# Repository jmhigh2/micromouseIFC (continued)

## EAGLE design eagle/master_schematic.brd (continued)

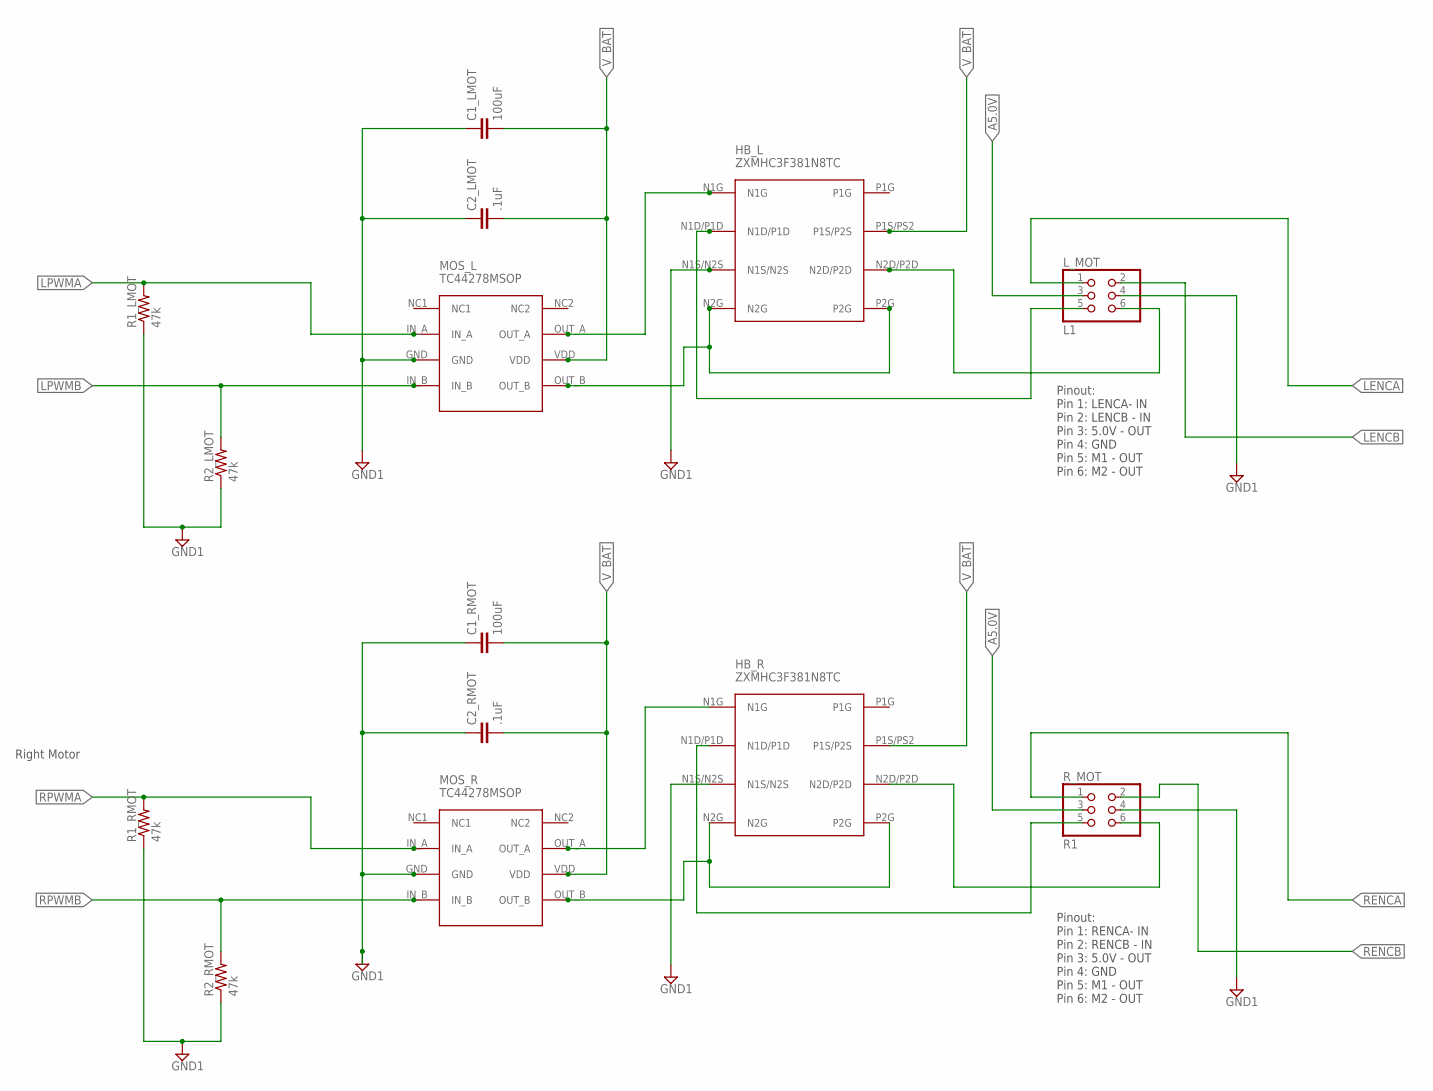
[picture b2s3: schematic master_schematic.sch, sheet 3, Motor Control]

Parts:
C1_LMOT, C1_RMOT: 100uF; C0603
C2_LMOT, C2_RMOT: .1uF; C0603
HB_L: ZXMHC3F381N8TC; 8-SOIC
HB_R: ZXMHC3F381N8TC; 8-SOIC
L_MOT: L1; 2X03
MOS_L: TC44278MSOP
MOS_R: TC44278MSOP
R1_LMOT, R1_RMOT, R2_LMOT, R2_RMOT: 47k; R0603
R_MOT: R1; 2X03

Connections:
A5.0V: L_MOT.3, R_MOT.3; also elsewhere on the board
GND1: C1_LMOT.1, C1_RMOT.1, C2_LMOT.1, C2_RMOT.1, HB_L.N1S/N2S, HB_R.N1S/N2S, L_MOT.4, MOS_L.GND, MOS_R.GND, R1_LMOT.1, R1_RMOT.1, R2_LMOT.1, R2_RMOT.1, R_MOT.4
LPWMA: MOS_L.IN_A, R1_LMOT.2; also elsewhere on the board
LPWMB: MOS_L.IN_B, R2_LMOT.2; also elsewhere on the board
L_ENC_A: L_MOT.1; also elsewhere on the board
L_ENC_B: L_MOT.2; also elsewhere on the board
unnamed: HB_L.N1G, MOS_L.OUT_A
unnamed: HB_L.N2G, HB_L.P2G, MOS_L.OUT_B
unnamed: HB_L.N1D/P1D, L_MOT.5
unnamed: HB_L.N2D/P2D, L_MOT.6
unnamed: HB_R.N1G, MOS_R.OUT_A
unnamed: HB_R.N2G, HB_R.P2G, MOS_R.OUT_B
unnamed: HB_R.N1D/P1D, R_MOT.5
unnamed: HB_R.N2D/P2D, R_MOT.6
RPWMA: MOS_R.IN_A, R1_RMOT.2; also elsewhere on the board
RPWMB: MOS_R.IN_B, R2_RMOT.2; also elsewhere on the board
R_ENC_A: R_MOT.1; also elsewhere on the board
R_ENC_B: R_MOT.2; also elsewhere on the board
V_BAT: C1_LMOT.2, C1_RMOT.2, C2_LMOT.2, C2_RMOT.2, HB_L.P1S/PS2 (P1S/P2S), HB_R.P1S/PS2 (P1S/P2S), MOS_L.VDD, MOS_R.VDD; also elsewhere on the board

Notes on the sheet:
Pinout: Pin 1: LENCA- IN Pin 2: LENCB - IN Pin 3: 5.0V - OUT Pin 4: GND Pin 5: M1 - OUT Pin 6: M2 - OUT
Right Motor
Pinout: Pin 1: RENCA- IN Pin 2: RENCB - IN Pin 3: 5.0V - OUT Pin 4: GND Pin 5: M1 - OUT Pin 6: M2 - OUT

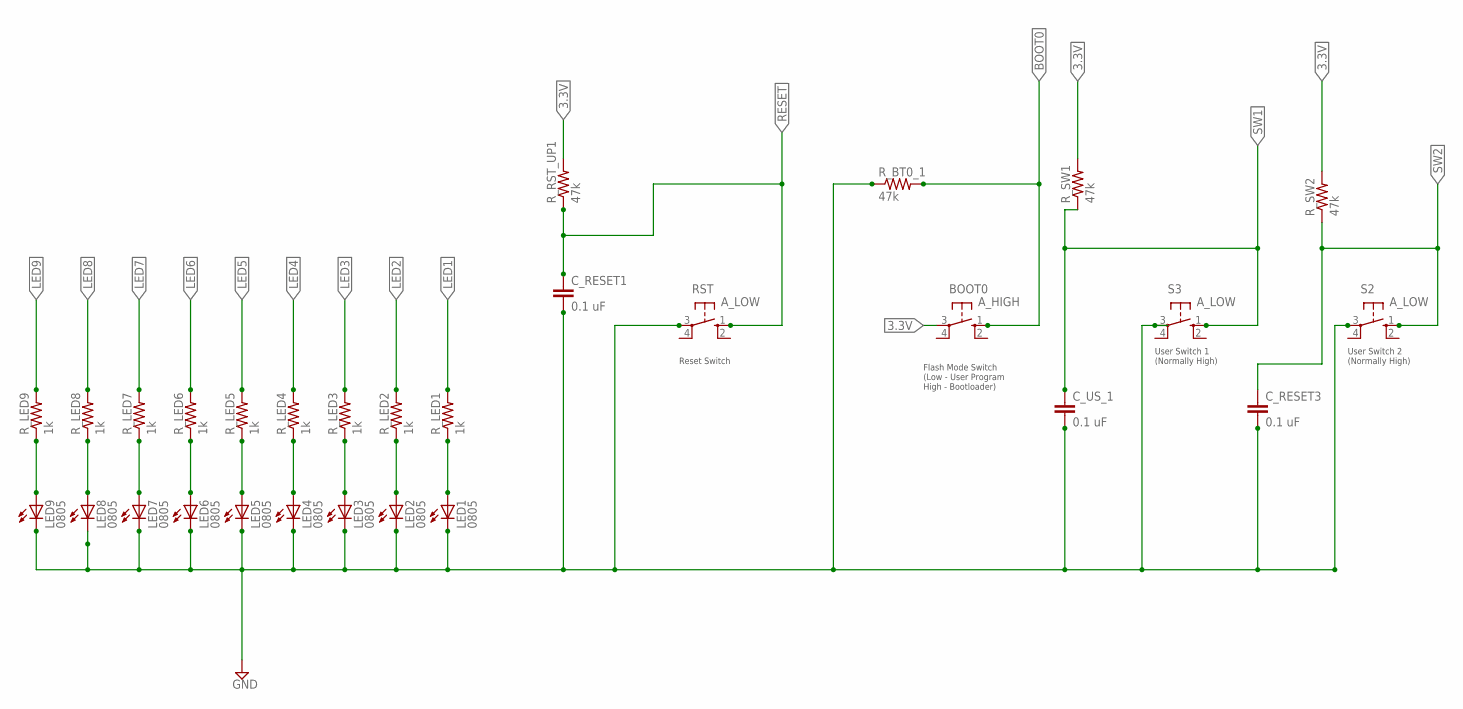
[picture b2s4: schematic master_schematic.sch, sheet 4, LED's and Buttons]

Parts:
BOOT0: A_HIGH; B3F-10XX
C_RESET1, C_RESET3: 0.1 uF; C0603
C_US_1: 0.1 uF; C0603
LED1, LED2, LED3, LED4, LED5, LED6, LED7, LED8, LED9: 0805; CHIPLED_0603
RST: A_LOW; B3F-10XX
R_BT0_1: 47k; R0603
R_LED1, R_LED2, R_LED3, R_LED4, R_LED5, R_LED6, R_LED7, R_LED8, R_LED9: 1k; R0603
R_RST_UP1: 47k; R0603
R_SW1, R_SW2: 47k; R0603
S2, S3: A_LOW; B3F-10XX

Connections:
3.3V: BOOT0.3, R_RST_UP1.2, R_SW1.2, R_SW2.2; also elsewhere on the board
BOOT0: BOOT0.1 (S), R_BT0_1.2; also elsewhere on the board
C_US_2: C_RESET3.1, R_SW2.1, S2.1 (S)
GND: C_RESET1.2, C_RESET3.2, C_US_1.2, LED1.C, LED2.C, LED3.C, LED4.C, LED5.C, LED6.C, LED7.C, LED8.C, LED9.C, RST.3, R_BT0_1.1, S2.3, S3.3; also elsewhere on the board
LED1: R_LED1.2; also elsewhere on the board
LED2: R_LED2.2; also elsewhere on the board
LED3: R_LED3.2; also elsewhere on the board
LED4: R_LED4.2; also elsewhere on the board
LED5: R_LED5.2; also elsewhere on the board
LED6: R_LED6.2; also elsewhere on the board
LED7: R_LED7.2; also elsewhere on the board
LED8: R_LED8.2; also elsewhere on the board
LED9: R_LED9.2; also elsewhere on the board
unnamed: LED1.A, R_LED1.1
unnamed: LED2.A, R_LED2.1
unnamed: LED3.A, R_LED3.1
unnamed: LED4.A, R_LED4.1
unnamed: LED5.A, R_LED5.1
unnamed: LED6.A, R_LED6.1
unnamed: LED7.A, R_LED7.1
unnamed: LED8.A, R_LED8.1
unnamed: LED9.A, R_LED9.1
RESET: C_RESET1.1, RST.1 (S), R_RST_UP1.1; also elsewhere on the board
US_1: C_US_1.1, R_SW1.1, S3.1 (S)

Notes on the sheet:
Reset Switch
Flash Mode Switch (Low - User Program High - Bootloader)
User Switch 1 (Normally High)
User Switch 2 (Normally High)

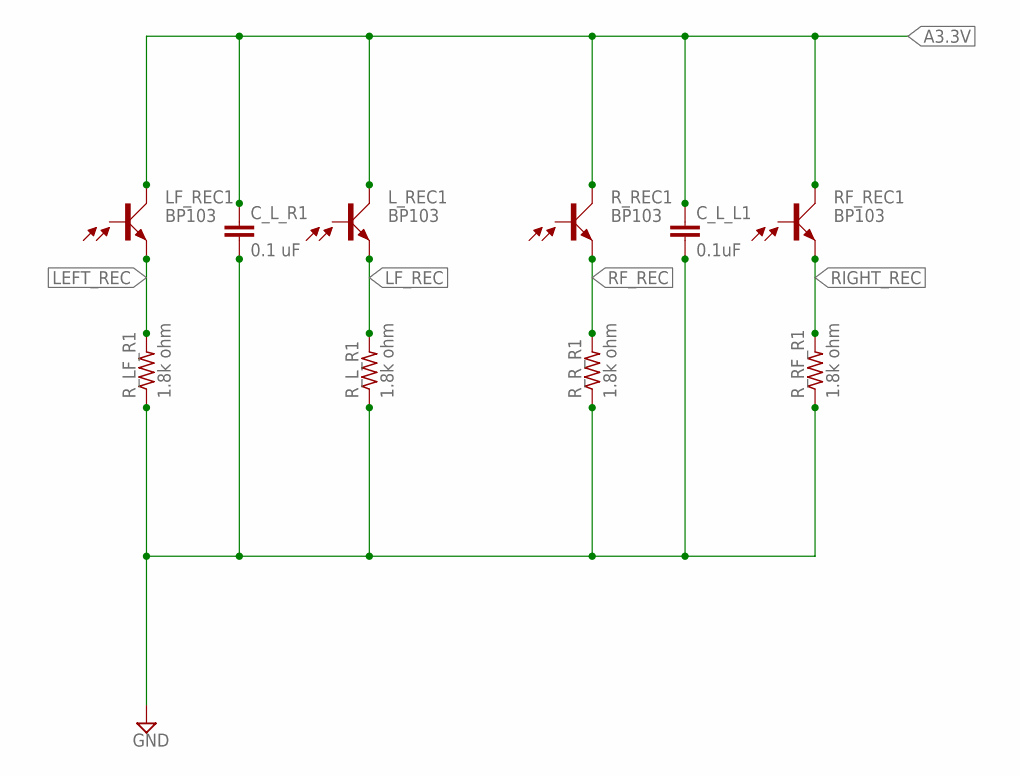
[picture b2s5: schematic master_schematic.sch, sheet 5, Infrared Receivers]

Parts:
C_L_L1: 0.1uF; C0603
C_L_R1: 0.1 uF; C0603
LF_REC1: BP103
L_REC1: BP103
RF_REC1: BP103
R_LF_R1: 1.8k ohm; R0603
R_L_R1: 1.8k ohm; R0603
R_REC1: BP103
R_RF_R1: 1.8k ohm; R0603
R_R_R1: 1.8k ohm; R0603

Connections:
A3.3V: C_L_L1.1, C_L_R1.1, LF_REC1.C, L_REC1.C, RF_REC1.C, R_REC1.C; also elsewhere on the board
GND: C_L_L1.2, C_L_R1.2, R_LF_R1.1, R_L_R1.1, R_RF_R1.1, R_R_R1.1; also elsewhere on the board
LEFT_REC: LF_REC1.E, R_LF_R1.2; also elsewhere on the board
LF_REC: L_REC1.E, R_L_R1.2; also elsewhere on the board
RF_REC: R_REC1.E, R_R_R1.2; also elsewhere on the board
RIGHT_REC: RF_REC1.E, R_RF_R1.2; also elsewhere on the board

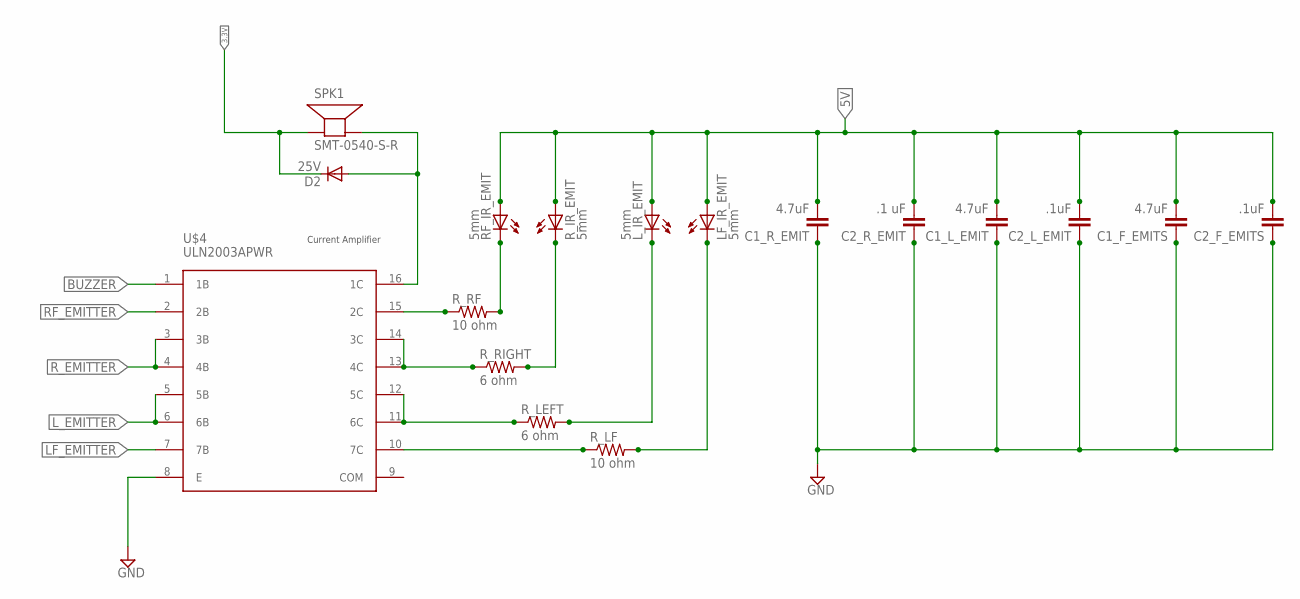
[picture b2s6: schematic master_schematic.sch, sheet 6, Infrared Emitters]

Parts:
C1_F_EMITS, C1_L_EMIT, C1_R_EMIT: 4.7uF; C1206
C2_F_EMITS, C2_L_EMIT: .1uF; C1206
C2_R_EMIT: .1 uF; C1206
D2: 25V; SOD123
LF_IR_EMIT: 5mm; LED5MM
L_IR_EMIT: 5mm; LED5MM
RF_IR_EMIT: 5mm; LED5MM
R_IR_EMIT: 5mm; LED5MM
R_LEFT: 6 ohm; R1206
R_LF: 10 ohm; R1206
R_RF: 10 ohm; R1206
R_RIGHT: 6 ohm; R1206
SPK1: SMT-0540-S-R
U$4: ULN2003APWR; 16-PINSOIC

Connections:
3.3V: D2.C, SPK1.- (+); also elsewhere on the board
5V: C1_F_EMITS.2, C1_L_EMIT.2, C1_R_EMIT.2, C2_F_EMITS.2, C2_L_EMIT.2, C2_R_EMIT.2, LF_IR_EMIT.A, L_IR_EMIT.A, RF_IR_EMIT.A, R_IR_EMIT.A; also elsewhere on the board
BUZZER: U$4.1 (1B); also elsewhere on the board
GND: C1_F_EMITS.1, C1_L_EMIT.1, C1_R_EMIT.1, C2_F_EMITS.1, C2_L_EMIT.1, C2_R_EMIT.1, U$4.8 (E); also elsewhere on the board
LF_EMITTER: U$4.7 (7B); also elsewhere on the board
L_EMITTER: U$4.5 (5B), U$4.6 (6B); also elsewhere on the board
unnamed: R_RF.1, U$4.15 (2C)
unnamed: RF_IR_EMIT.K (C), R_RF.2
unnamed: R_RIGHT.1, U$4.13 (4C), U$4.14 (3C)
unnamed: R_IR_EMIT.K (C), R_RIGHT.2
unnamed: L_IR_EMIT.K (C), R_LEFT.2
unnamed: R_LEFT.1, U$4.11 (6C), U$4.12 (5C)
unnamed: LF_IR_EMIT.K (C), R_LF.2
unnamed: D2.A, SPK1.+ (-), U$4.16 (1C)
unnamed: R_LF.1, U$4.10 (7C)
RF_EMITTER: U$4.2 (2B); also elsewhere on the board
R_EMITTER: U$4.3 (3B), U$4.4 (4B); also elsewhere on the board

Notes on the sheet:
Current Amplifier

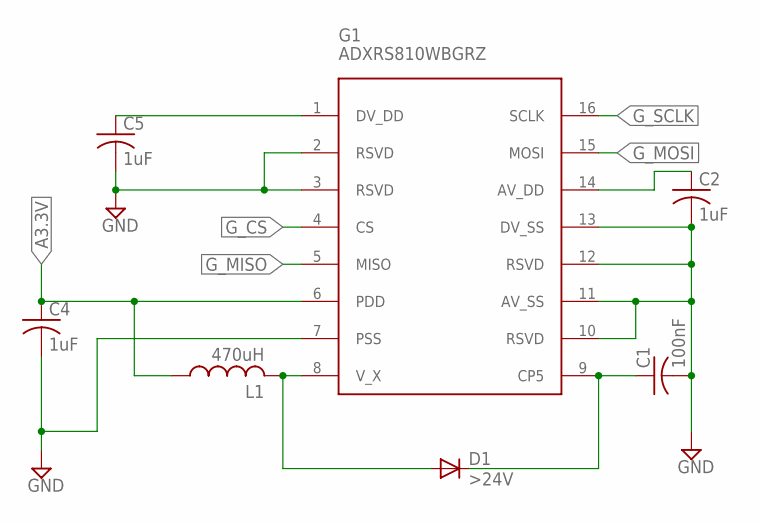
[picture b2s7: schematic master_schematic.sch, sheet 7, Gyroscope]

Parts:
C1: 100nF; C0603
C2, C4, C5: 1uF; C0603
D1: >24V; SOD123
G1: ADXRS810; SOIC-16
L1: 470uH; L1812

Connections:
A3.3V: C4.1, G1.6 (PDD), L1.1; also elsewhere on the board
GND: C1.2, C2.2, C4.2, C5.2, G1.2 (RSVD), G1.3 (RSVD), G1.7 (PSS), G1.10 (RSVD), G1.11 (AV_SS), G1.12 (RSVD), G1.13 (DV_SS); also elsewhere on the board
G_CS: G1.4 (CS); also elsewhere on the board
G_MISO: G1.5 (MISO); also elsewhere on the board
G_MOSI: G1.15 (MOSI); also elsewhere on the board
G_SCLK: G1.16 (SCLK); also elsewhere on the board
unnamed: C5.1, G1.1 (DV_DD)
unnamed: D1.A, G1.8 (V_X), L1.2
unnamed: C1.1, D1.C, G1.9 (CP5)
unnamed: C2.1, G1.14 (AV_DD)

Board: 2 copper layers, 105 parts (0 on the bottom side), 81 nets, no tracks yet.

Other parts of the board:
U$2: T212031

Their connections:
unnamed 54: U$2.2; also elsewhere on the board
V_BAT: U$2.3; also elsewhere on the board

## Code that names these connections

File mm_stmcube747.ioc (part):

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Mcu.Name=STM32F746V(E-G)Tx
Mcu.Package=LQFP100
Mcu.UserName=STM32F746VGTx
PA0/WKUP.GPIOParameters=GPIO_Label
PA0/WKUP.GPIO_Label=RPWMA
PA0/WKUP.Signal=S_TIM2_CH1_ETR
PA1.GPIOParameters=GPIO_Label
PA1.GPIO_Label=RPWMB
PA1.Signal=S_TIM2_CH2
PA10.Mode=Asynchronous
PA10.Signal=USART1_RX
PA13.Mode=Serial_Wire
PA13.Signal=SYS_JTMS-SWDIO
PA14.Mode=Serial_Wire
PA14.Signal=SYS_JTCK-SWCLK
PA2.GPIOParameters=GPIO_Label
PA2.GPIO_Label=LPWMA
PA2.Signal=S_TIM2_CH3
PA3.GPIOParameters=GPIO_Label
PA3.GPIO_Label=LPWMB
PA3.Signal=S_TIM2_CH4
PA4.GPIOParameters=GPIO_Label
PA4.GPIO_Label=GYRO_CS
PA4.Signal=GPIO_Output
PA5.GPIOParameters=GPIO_Label
PA5.GPIO_Label=GYRO_SCLK
PA5.Mode=Full_Duplex_Master
PA5.Signal=SPI1_SCK
PA6.GPIOParameters=GPIO_Label
PA6.GPIO_Label=GYRO_MISO
PA6.Mode=Full_Duplex_Master
PA6.Signal=SPI1_MISO
PA7.GPIOParameters=GPIO_Label
PA7.GPIO_Label=GYRO_MOSI
PA7.Mode=Full_Duplex_Master
PA7.Signal=SPI1_MOSI
PA9.Mode=Asynchronous
PA9.Signal=USART1_TX
PB0.GPIOParameters=GPIO_Label
PB0.GPIO_Label=RF_REC
PB0.Signal=ADCx_IN8
PB1.GPIOParameters=GPIO_Label
PB1.GPIO_Label=R_REC
PB1.Signal=ADCx_IN9
PB12.GPIOParameters=GPIO_Label
PB12.GPIO_Label=LED1
PB12.Signal=GPIO_Output
PB13.GPIOParameters=GPIO_Label
PB13.GPIO_Label=LED2
PB13.Signal=GPIO_Output
PB14.GPIOParameters=GPIO_Label
PB14.GPIO_Label=LED3
PB14.Signal=GPIO_Output
PB4.GPIOParameters=GPIO_Label
PB4.GPIO_Label=LF_EMIT
PB4.Signal=S_TIM3_CH1
PB5.GPIOParameters=GPIO_Label
PB5.GPIO_Label=L_EMIT
PB5.Signal=S_TIM3_CH2
PC0.GPIOParameters=GPIO_Label
PC0.GPIO_Label=VOLTMETER
PC0.Signal=ADCx_IN10
PC1.GPIOParameters=GPIO_Label
PC1.GPIO_Label=LED5
PC1.Signal=GPIO_Output
PC2.GPIOParameters=GPIO_Label
PC2.GPIO_Label=LED4
PC2.Signal=GPIO_Output
PC4.GPIOParameters=GPIO_Label
PC4.GPIO_Label=L_REC
PC4.Signal=ADCx_IN14
PC5.GPIOParameters=GPIO_Label
PC5.GPIO_Label=LF_REC
PC5.Signal=ADCx_IN15
PC6.GPIOParameters=GPIO_Label
PC6.GPIO_Label=SW1
PC6.Signal=GPIO_Input
PC8.GPIOParameters=GPIO_Label
PC8.GPIO_Label=R_EMIT
PC8.Signal=S_TIM3_CH3
PC9.GPIOParameters=GPIO_Label
PC9.GPIO_Label=RF_EMIT
PC9.Signal=S_TIM3_CH4
PD12.GPIOParameters=GPIO_Label
PD12.GPIO_Label=BUZZER
PD12.Signal=S_TIM4_CH1
PD15.GPIOParameters=GPIO_Label
PD15.GPIO_Label=SW2
PD15.Signal=GPIO_Input
PD2.GPIOParameters=GPIO_Label
PD2.GPIO_Label=LED9
PD2.Signal=GPIO_Output
PD3.GPIOParameters=GPIO_Label
PD3.GPIO_Label=LED8
PD3.Signal=GPIO_Output
PD4.GPIOParameters=GPIO_Label
PD4.GPIO_Label=LED7
PD4.Signal=GPIO_Output
PD5.GPIOParameters=GPIO_Label
PD5.GPIO_Label=LED6
PD5.Signal=GPIO_Output
PE11.GPIOParameters=GPIO_Label
PE11.GPIO_Label=LENC_CHA
PE11.Signal=S_TIM1_CH2
PE13.GPIOParameters=GPIO_Label
PE13.GPIO_Label=RENC_CHB
PE13.Signal=S_TIM1_CH3
PE14.GPIOParameters=GPIO_Label
PE14.GPIO_Label=RENC_CHA
PE14.Signal=S_TIM1_CH4
PE9.GPIOParameters=GPIO_Label
PE9.GPIO_Label=LENC_CHB
PE9.Signal=S_TIM1_CH1
RCC.HSE_VALUE=25000000

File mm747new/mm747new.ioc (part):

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Mcu.Name=STM32F746V(E-G)Tx
Mcu.Package=LQFP100
Mcu.UserName=STM32F746VGTx
PA0/WKUP.GPIOParameters=GPIO_Label
PA0/WKUP.GPIO_Label=RPWMA
PA0/WKUP.Signal=S_TIM2_CH1_ETR
PA1.GPIOParameters=GPIO_Label
PA1.GPIO_Label=RPWMB
PA1.Signal=S_TIM2_CH2
PA10.Mode=Asynchronous
PA10.Signal=USART1_RX
PA13.Mode=Serial_Wire
PA13.Signal=SYS_JTMS-SWDIO
PA14.Mode=Serial_Wire
PA14.Signal=SYS_JTCK-SWCLK
PA2.GPIOParameters=GPIO_Label
PA2.GPIO_Label=LPWMA
PA2.Signal=S_TIM2_CH3
PA3.GPIOParameters=GPIO_Label
PA3.GPIO_Label=LPWMB
PA3.Signal=S_TIM2_CH4
PA4.GPIOParameters=GPIO_Label
PA4.GPIO_Label=GYRO_CS
PA4.Signal=GPIO_Output
PA5.GPIOParameters=GPIO_Label
PA5.GPIO_Label=GYRO_SCLK
PA5.Mode=Full_Duplex_Master
PA5.Signal=SPI1_SCK
PA6.GPIOParameters=GPIO_Label
PA6.GPIO_Label=GYRO_MISO
PA6.Mode=Full_Duplex_Master
PA6.Signal=SPI1_MISO
PA7.GPIOParameters=GPIO_Label
PA7.GPIO_Label=GYRO_MOSI
PA7.Mode=Full_Duplex_Master
PA7.Signal=SPI1_MOSI
PA9.Mode=Asynchronous
PA9.Signal=USART1_TX
PB0.GPIOParameters=GPIO_Label
PB0.GPIO_Label=RF_REC
PB0.Signal=ADCx_IN8
PB1.GPIOParameters=GPIO_Label
PB1.GPIO_Label=R_REC
PB1.Signal=ADCx_IN9
PB4.GPIOParameters=GPIO_Label
PB4.GPIO_Label=RENCB
PB4.Signal=S_TIM3_CH1
PB5.GPIOParameters=GPIO_Label
PB5.GPIO_Label=RENCA
PB5.Signal=S_TIM3_CH2
PB8.GPIOParameters=GPIO_Label
PB8.GPIO_Label=R_EMIT
PB8.Signal=GPIO_Output
PB9.GPIOParameters=GPIO_Label
PB9.GPIO_Label=RF_EMIT
PB9.Signal=GPIO_Output
PC4.GPIOParameters=GPIO_Label
PC4.GPIO_Label=L_REC
PC4.Signal=ADCx_IN14
PC5.GPIOParameters=GPIO_Label
PC5.GPIO_Label=LF_REC
PC5.Signal=ADCx_IN15
PC6.GPIOParameters=GPIO_Label
PC6.GPIO_Label=BUTTON2
PC6.Signal=GPXTI6
PD1.GPIOParameters=GPIO_Label
PD1.GPIO_Label=LED5
PD1.Signal=GPIO_Output
PD12.GPIOParameters=GPIO_Label
PD12.GPIO_Label=BUZZER
PD12.Signal=S_TIM4_CH1
PD15.GPIOParameters=GPIO_Label
PD15.GPIO_Label=BUTTON1
PD15.Signal=GPXTI15
PD2.GPIOParameters=GPIO_Label
PD2.GPIO_Label=LED4
PD2.Signal=GPIO_Output
PD3.GPIOParameters=GPIO_Label
PD3.GPIO_Label=LED3
PD3.Signal=GPIO_Output
PD4.GPIOParameters=GPIO_Label
PD4.GPIO_Label=LED2
PD4.Signal=GPIO_Output
PD5.GPIOParameters=GPIO_Label
PD5.GPIO_Label=LED1
PD5.Signal=GPIO_Output
PE0.GPIOParameters=GPIO_Label
PE0.GPIO_Label=LF_EMIT
PE0.Signal=GPIO_Output
PE1.GPIOParameters=GPIO_Label
PE1.GPIO_Label=L_EMIT
PE1.Signal=GPIO_Output
PE11.GPIOParameters=GPIO_Label
PE11.GPIO_Label=LENC_CHA
PE11.Signal=S_TIM1_CH2
PE9.GPIOParameters=GPIO_Label
PE9.GPIO_Label=LENC_CHB
PE9.Signal=S_TIM1_CH1
RCC.HSE_VALUE=25000000
board=mm747new

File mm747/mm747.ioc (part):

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Mcu.Name=STM32F746V(E-G)Tx
Mcu.Package=LQFP100
Mcu.UserName=STM32F746VGTx
PA0/WKUP.GPIOParameters=GPIO_Label
PA0/WKUP.GPIO_Label=LPWM
PA0/WKUP.Signal=S_TIM2_CH1_ETR
PA1.GPIOParameters=GPIO_Label
PA1.GPIO_Label=LDIC
PA1.Signal=GPIO_Output
PA10.Mode=Asynchronous
PA10.Signal=USART1_RX
PA13.Mode=Serial_Wire
PA13.Signal=SYS_JTMS-SWDIO
PA14.Mode=Serial_Wire
PA14.Signal=SYS_JTCK-SWCLK
PA2.GPIOParameters=GPIO_Label
PA2.GPIO_Label=RPWM
PA2.Signal=S_TIM2_CH3
PA3.GPIOParameters=GPIO_Label
PA3.GPIO_Label=RDIC
PA3.Signal=GPIO_Output
PA4.GPIOParameters=GPIO_Label
PA4.GPIO_Label=GYRO_CS
PA4.Signal=GPIO_Output
PA5.GPIOParameters=GPIO_Label
PA5.GPIO_Label=GYRO_SCLK
PA5.Mode=Full_Duplex_Master
PA5.Signal=SPI1_SCK
PA6.GPIOParameters=GPIO_Label
PA6.GPIO_Label=GYRO_MISO
PA6.Mode=Full_Duplex_Master
PA6.Signal=SPI1_MISO
PA7.GPIOParameters=GPIO_Label
PA7.GPIO_Label=GYRO_MOSI
PA7.Mode=Full_Duplex_Master
PA7.Signal=SPI1_MOSI
PA9.Mode=Asynchronous
PA9.Signal=USART1_TX
PB0.GPIOParameters=GPIO_Label
PB0.GPIO_Label=RF_REC
PB0.Signal=ADCx_IN8
PB1.GPIOParameters=GPIO_Label
PB1.GPIO_Label=R_REC
PB1.Signal=ADCx_IN9
PB4.Signal=GPIO_Output
PB5.Signal=GPIO_Output
PB6.GPIOParameters=GPIO_Label
PB6.GPIO_Label=RENCA
PB6.Signal=S_TIM4_CH1
PB7.GPIOParameters=GPIO_Label
PB7.GPIO_Label=RENCB
PB7.Signal=S_TIM4_CH2
PC4.GPIOParameters=GPIO_Label
PC4.GPIO_Label=L_REC
PC4.Signal=ADCx_IN14
PC5.GPIOParameters=GPIO_Label
PC5.GPIO_Label=LF_REC
PC5.Signal=ADCx_IN15
PC6.GPIOParameters=GPIO_Label
PC6.GPIO_Label=BUTTON2
PC6.Signal=GPXTI6
PC8.Signal=GPIO_Output
PC9.Signal=GPIO_Output
PD1.GPIOParameters=GPIO_Label
PD1.GPIO_Label=LED5
PD1.Signal=GPIO_Output
PD15.GPIOParameters=GPIO_Label
PD15.GPIO_Label=BUTTON1
PD15.Signal=GPXTI15
PD2.GPIOParameters=GPIO_Label
PD2.GPIO_Label=LED4
PD2.Signal=GPIO_Output
PD3.GPIOParameters=GPIO_Label
PD3.GPIO_Label=LED3
PD3.Signal=GPIO_Output
PD4.GPIOParameters=GPIO_Label
PD4.GPIO_Label=LED2
PD4.Signal=GPIO_Output
PD5.GPIOParameters=GPIO_Label
PD5.GPIO_Label=LED1
PD5.Signal=GPIO_Output
PE11.GPIOParameters=GPIO_Label
PE11.GPIO_Label=LENCB
PE11.Signal=S_TIM1_CH2
PE5.GPIOParameters=GPIO_Label
PE5.GPIO_Label=BUZZer
PE5.Signal=S_TIM9_CH1
PE9.GPIOParameters=GPIO_Label
PE9.GPIO_Label=LENCA
PE9.Signal=S_TIM1_CH1
RCC.HSE_VALUE=25000000
RCC.SYSCLKFreq_VALUE=108000000
RCC.SYSCLKSource=RCC_SYSCLKSOURCE_PLLCLK
board=mm747

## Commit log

2016-09-17 Updated Folders
2016-09-19 Added Test JSON Maze
2016-09-19 Continued Work
2016-09-20 Working Mouse
2016-09-24 New Files
2016-09-24 Dick Picks
2016-09-24 Weiner
2016-09-24 Hello dickheads
2016-09-24 all files
2016-09-26 Working Python Code
2016-09-26 Test File
2016-09-26 i think i figured it out
2016-09-30 Completed Maze Solver
2016-09-30 Solved First Competition Maze
2016-10-03 Working mouse plot. Need pyplot to run
2016-10-04 Pyplot Visualization
2016-10-05 Pretty Graphs
2016-10-05 my file
2016-10-06 Eagle Folder
2016-10-06 dicks
2016-10-06 check out maze.cpp
2016-10-06 FLood works
2016-10-18 Linear Regulators
2016-10-19 suck dick pussy shit
2016-10-25 Microcontoller Schem
2016-10-25 2x3heder
2016-10-25 LED schematic and Motor Driver Schematic that is named power for some reason
2016-10-25 IR receiver system
2016-10-25 Bullshit
2016-10-27 Merged into Master
2016-10-27 New Schematic
2016-10-27 Schematic
2016-12-02 ir led schematic emitter
2016-12-02 Organization
2016-12-02 stuff
2016-12-02 Switch
2016-12-02 Comments
2016-12-03 Cleanup
2016-12-06 Updated Schematic + Gyroscope
2016-12-10 Added Buzzer
2016-12-20 Fixed Inductors
2016-12-24 Motor and Battery Mount
2016-12-27 added hbridge
2016-12-27 ULN and stuff
2017-01-07 Schematic Update
2017-01-07 Datasheets
2017-01-16 check before purchase
2017-01-20 hex file
2017-01-31 Updated Eagle LBR
2017-02-02 Clean directory
2017-02-02 Atollic Code
2017-02-10 Revision 2 Schem + Board + GERBS
2017-02-14 here is the fully function CPP file and header for flood fill, had to extract off of old computer
2017-02-14 Cube File
2017-02-14 Cube
2017-02-17 Updated IOC file
2017-02-19 Test HEX
2017-02-27 mouse revision # 3
2017-03-06 Updated Code 3.5.17
2017-03-06 Final Board
2017-03-13 Apparently this is the final PCB
2017-03-13 NEW PUSH
2017-03-13 Last Revision allegedly
2017-03-21 Updated main
2017-03-30 STUPID
2017-03-30 Comments up the ass
2017-04-01 Better Right Turns
2017-04-01 Stuff 4/1/17
2017-04-02 LATEST STUFF
2017-04-02 Last Commit
2017-04-03 Latest Update
2017-04-03 LATEST
2017-04-11 Don't Lose me bro
2017-04-13 PLEASE WORK
2017-04-17 april6th
2017-04-18 4.17.17
2017-04-21 Update 420
2017-04-30 HELP
2017-05-18 5/15/17
2017-05-23 MAY24
2017-08-18 Final main file
2021-11-13 committing code used for competition, working version of python floodfill
